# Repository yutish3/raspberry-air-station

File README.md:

# raspberry-air-station
this is a small project. how it overall works is raspberry pie takes data from sen 54 sensor and displayes it on e ink display and on a password protected website

deeper explanation :- it runs on a raspberry pi 4 and it uses sen 54 to get the info like (PM1.0, PM2.5, PM4.0, PM10, VOC Index, Temperature, Humidity) and display it on the e ink display which updates every 10 second and in background it is also hosting a website so you can change image on the aqi sensor like black and white art from phone and can also access the aqi data from website and the website is password protected. there is also an physical touch sensor using which you can switch between what to show on e ink display photo or the data 

i decided to make this project so i can have it as my personal home air station as i live in delhi (avg 300+ aqi) i will prob use it a lot to check the aqi and it can give an overall glimps of if i should leave the state for now or not 

# BOM
1. Sensirion SEN54 - 1 - Air Quality Sensor
2. Raspberry Pi 4 Model B (4GB RAM) - 1 - main controller
3. Waveshare 4.2-inch e-Paper Module (SPI) - 1 - display (400x300)
4. SmartElex Logic Level Converter (Bi-Directional) - 1 - 4 channel bi direction converter (3.3v - 5v)
5. Raspberry Pi 4 Power Supply (5.1V 3A Type-C) - 1 - power supply
6. Male Headers (1x40 Pin, 2.54mm) - 1
7. Female Headers (2x20 Pin, 2.54mm) - 1 
8. TTP223 Touch Sensor (Module) - 1 - input sensor
9 sd card 32 gb - 1 - for storage

i found all the components on robu except SEN54 which i found on Tanotis

# BOM images

# CAD FILE

# PCM

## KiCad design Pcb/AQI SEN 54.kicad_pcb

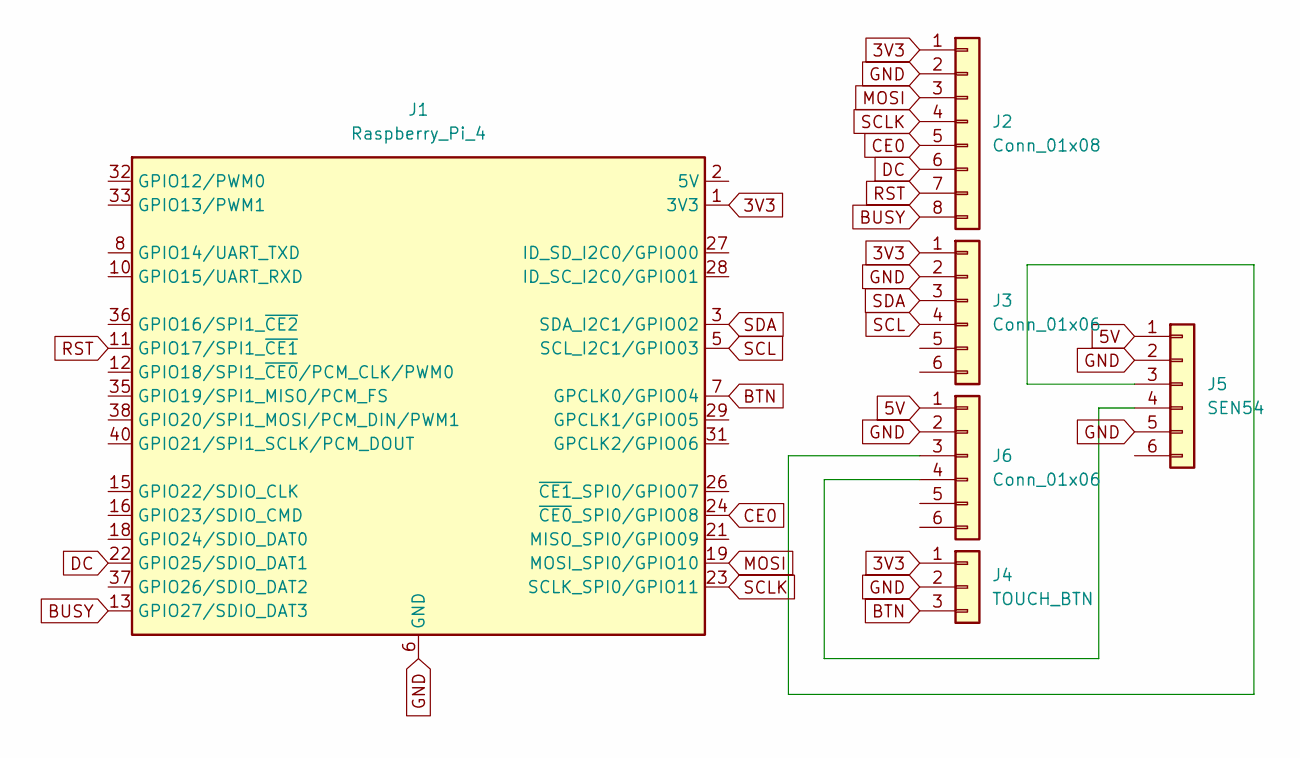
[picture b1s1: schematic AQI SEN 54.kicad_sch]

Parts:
J1: Raspberry_Pi_4; PinSocket_2x20_P2.54mm_Vertical
J2: Conn_01x08; PinHeader_1x08_P2.54mm_Vertical
J3, J6: Conn_01x06; PinHeader_1x06_P2.54mm_Vertical
J4: TOUCH_BTN; PinHeader_1x03_P2.54mm_Vertical
J5: SEN54; PinHeader_1x06_P2.54mm_Vertical

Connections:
3V3: J1.1 (3V3), J1.17 (3V3), J2.1, J3.1, J4.1
5V: J5.1, J6.1
BTN: J1.7 (GPCLK0/GPIO04), J4.3
BUSY: J1.13 (GPIO27/SDIO_DAT3), J2.8
CE0: J1.24 (~CE0_SPI0/GPIO08), J2.5
DC: J1.22 (GPIO25/SDIO_DAT1), J2.6
GND: J1.6 (GND), J1.9 (GND), J1.14 (GND), J1.20 (GND), J1.25 (GND), J1.30 (GND), J1.34 (GND), J1.39 (GND), J2.2, J3.2, J4.2, J5.2, J5.5, J6.2
MOSI: J1.19 (MOSI_SPI0/GPIO10), J2.3
unnamed: J1.2 (5V), J1.4 (5V)
unnamed: J5.3, J6.3
unnamed: J5.4, J6.4
RST: J1.11 (GPIO17/SPI1_~CE1), J2.7
SCL: J1.5 (SCL_I2C1/GPIO03), J3.4
SCLK: J1.23 (SCLK_SPI0/GPIO11), J2.4
SDA: J1.3 (SDA_I2C1/GPIO02), J3.3

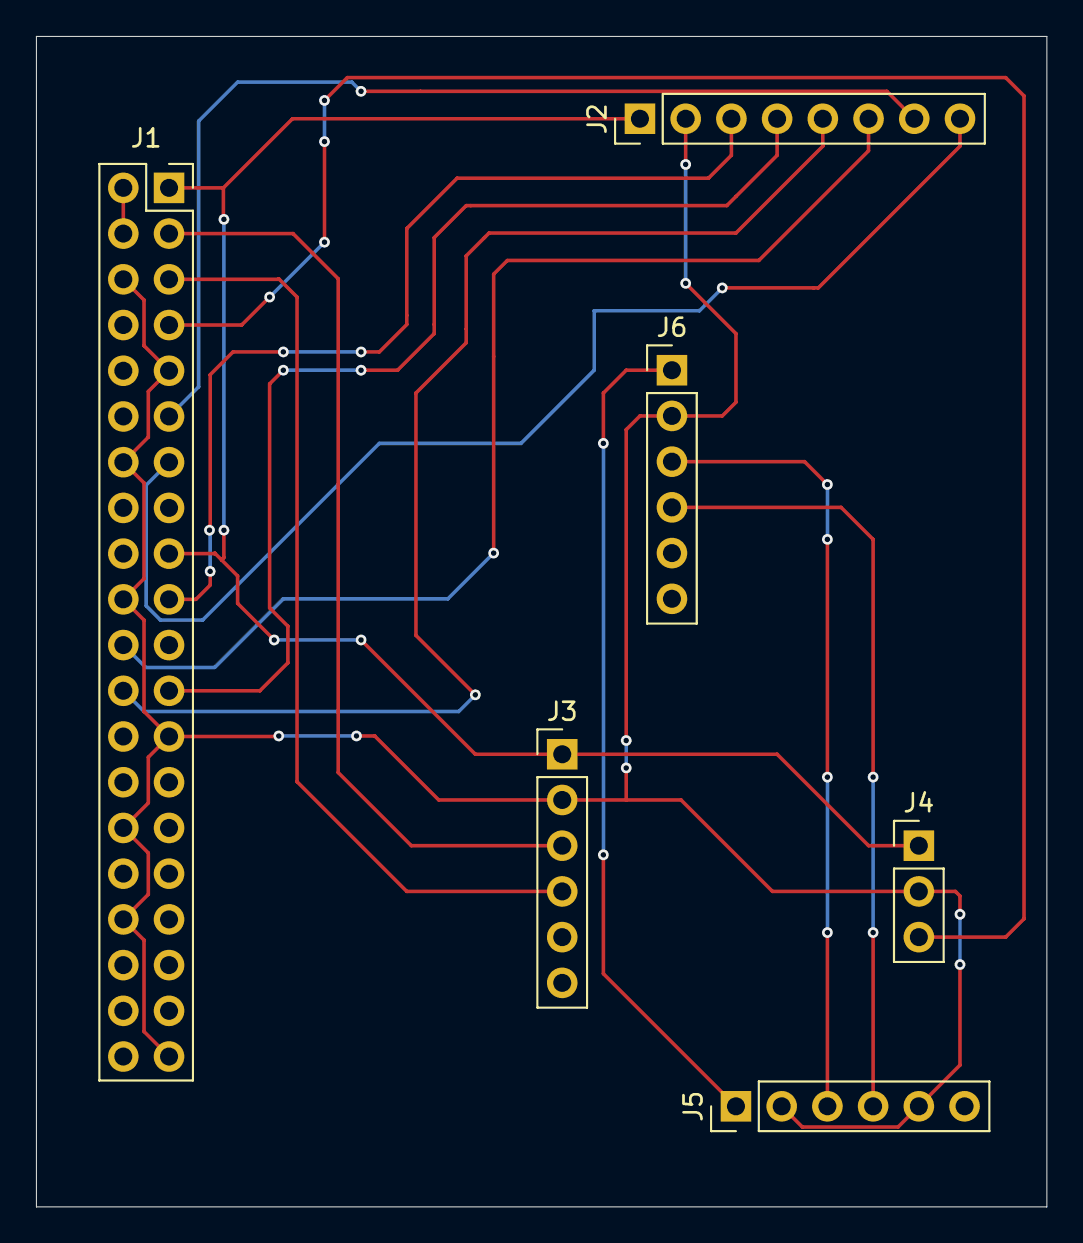
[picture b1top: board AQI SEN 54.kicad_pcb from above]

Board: 2 copper layers, 56.1 x 65.0 mm, 6 parts (0 on the bottom side), 15 nets.

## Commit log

2025-12-18 cad and pcb
2025-12-18 Add README for raspberry-air-station project
    This README provides an overview of the raspberry-air-station project, detailing its functionality, components, and images.
2025-12-18 firmware
2025-12-18 Add 32GB SD card to components list
    Added mention of 32GB SD card for storage.
2025-12-18 Add BOM images to README
    Added additional BOM images to the README.
2025-12-18 Add BOM.CSV with component details and costs
2025-12-18 Create BOM.csv with component details
    Added a Bill of Materials (BOM) with parts, quantities, vendors, and costs.
2025-12-19 Add BOM images section to README
